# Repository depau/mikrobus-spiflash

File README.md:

# mikroBUS SPI flash module

Sporting 2 removable SPI NOR flash memories, interchangeable. Useful to swap and reprogram the firmware of the GlobalScale MOCHAbin.

The top tiny boards are supposed to be broken off and installed on the pin headers.

The switch allows switching between the two flash memories.

I've ordered the boards but I haven't received/tested them yet.

## License

CERN Open Hardware License, strictly reciprocal.

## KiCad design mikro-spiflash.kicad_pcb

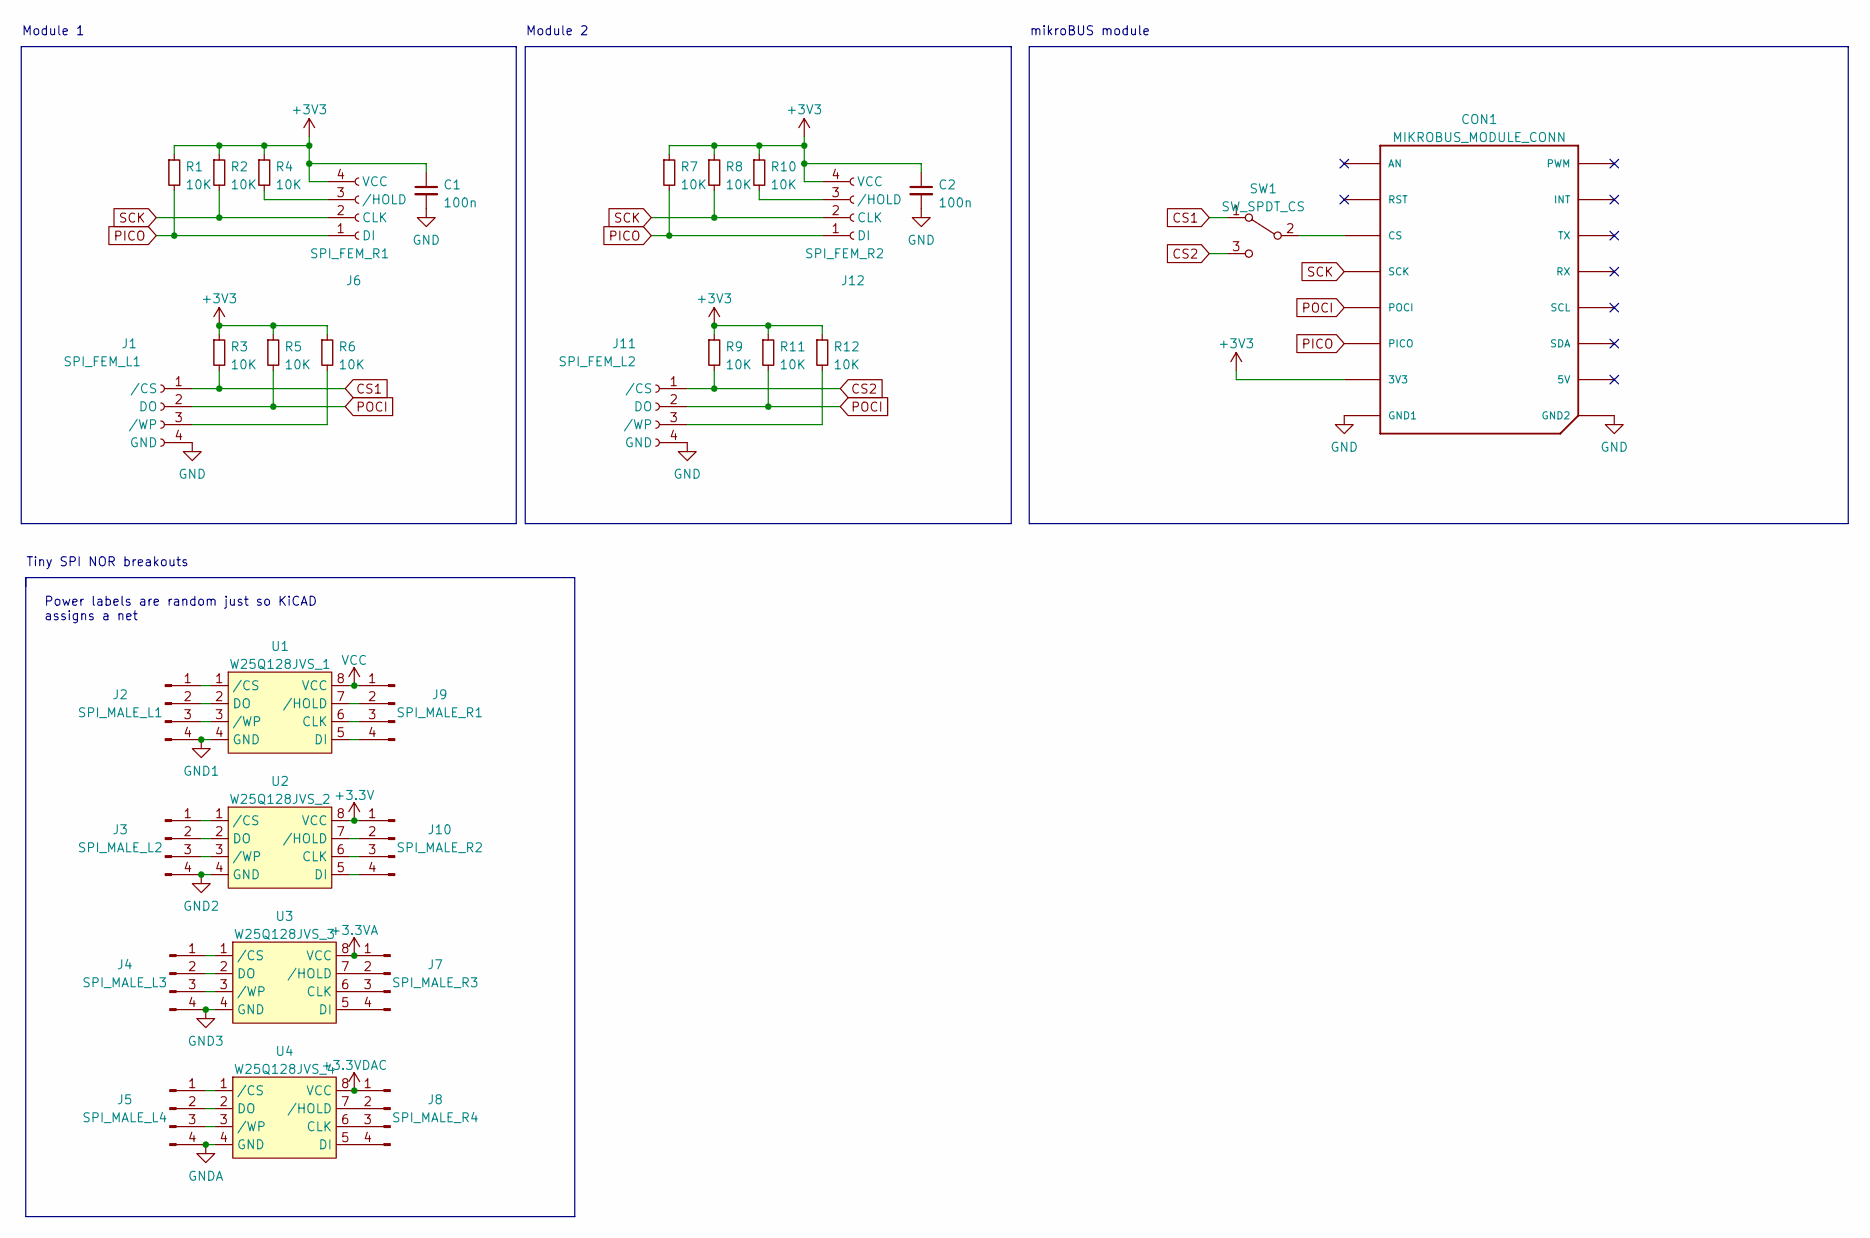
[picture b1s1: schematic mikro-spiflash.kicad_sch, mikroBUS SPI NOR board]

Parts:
C1, C2: 100n; C_0402_1005Metric; JLCPCB BOM 1
CON1: MIKROBUS_MODULE_CONN; JLCPCB BOM 0
J1: SPI_FEM_L1; PinSocket_1x04_P2.54mm_Vertical; JLCPCB BOM 0
J2: SPI_MALE_L1; PinHeader_1x04_P2.54mm_Vertical; JLCPCB BOM 0
J3: SPI_MALE_L2; PinHeader_1x04_P2.54mm_Vertical; JLCPCB BOM 0
J4: SPI_MALE_L3; PinHeader_1x04_P2.54mm_Vertical; JLCPCB BOM 0
J5: SPI_MALE_L4; PinHeader_1x04_P2.54mm_Vertical; JLCPCB BOM 0
J6: SPI_FEM_R1; PinSocket_1x04_P2.54mm_Vertical; JLCPCB BOM 0
J7: SPI_MALE_R3; PinHeader_1x04_P2.54mm_Vertical; JLCPCB BOM 0
J8: SPI_MALE_R4; PinHeader_1x04_P2.54mm_Vertical; JLCPCB BOM 0
J9: SPI_MALE_R1; PinHeader_1x04_P2.54mm_Vertical; JLCPCB BOM 0
J10: SPI_MALE_R2; PinHeader_1x04_P2.54mm_Vertical; JLCPCB BOM 0
J11: SPI_FEM_L2; PinSocket_1x04_P2.54mm_Vertical; JLCPCB BOM 0
J12: SPI_FEM_R2; PinSocket_1x04_P2.54mm_Vertical; JLCPCB BOM 0
R1, R2, R3, R4, R5, R6, R7, R8, R9, R10, R11, R12: 10K; R_0402_1005Metric; JLCPCB BOM 1
SW1: SW_SPDT_CS; SW_MSK12C02-HB; JLCPCB BOM 1
U1: W25Q128JVS_1; SOIC-8_5.23x5.23mm_P1.27mm; JLCPCB BOM 1
U2: W25Q128JVS_2; SOIC-8_5.23x5.23mm_P1.27mm; JLCPCB BOM 1
U3: W25Q128JVS_3; SOIC-8_5.23x5.23mm_P1.27mm; JLCPCB BOM 1
U4: W25Q128JVS_4; SOIC-8_5.23x5.23mm_P1.27mm; JLCPCB BOM 1

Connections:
+3.3V: J10.1, U2.8 (VCC)
+3.3VA: J7.1, U3.8 (VCC)
+3.3VDAC: J8.1, U4.8 (VCC)
+3V3: C1.1, C2.1, CON1.P7 (3V3), J6.4 (VCC), J12.4 (VCC), R1.1, R2.1, R3.1, R4.1, R5.1, R6.1, R7.1, R8.1, R9.1, R10.1, R11.1, R12.1
CS1: J1.1 (/CS), R3.2, SW1.1 (A)
CS2: J11.1 (/CS), R9.2, SW1.3 (C)
GND: C1.2, C2.2, CON1.P8 (GND1), CON1.P9 (GND2), J1.4 (GND), J11.4 (GND)
GND1: J2.4, U1.4 (GND)
GND2: J3.4, U2.4 (GND)
GND3: J4.4, U3.4 (GND)
GNDA: J5.4, U4.4 (GND)
unnamed: CON1.P3 (CS), SW1.2 (B)
unnamed: J1.3 (/WP), R6.2
unnamed: J2.1, U1.1 (/CS)
unnamed: J2.2, U1.2 (DO)
unnamed: J2.3, U1.3 (/WP)
unnamed: J6.3 (/HOLD), R4.2
unnamed: J11.3 (/WP), R12.2
unnamed: J12.3 (/HOLD), R10.2
unnamed: J9.4, U1.5 (DI)
unnamed: J9.3, U1.6 (CLK)
unnamed: J9.2, U1.7 (/HOLD)
unnamed: J3.1, U2.1 (/CS)
unnamed: J3.2, U2.2 (DO)
unnamed: J3.3, U2.3 (/WP)
unnamed: J10.4, U2.5 (DI)
unnamed: J10.3, U2.6 (CLK)
unnamed: J10.2, U2.7 (/HOLD)
unnamed: J4.1, U3.1 (/CS)
unnamed: J4.2, U3.2 (DO)
unnamed: J4.3, U3.3 (/WP)
unnamed: J7.4, U3.5 (DI)
unnamed: J7.3, U3.6 (CLK)
unnamed: J7.2, U3.7 (/HOLD)
unnamed: J5.1, U4.1 (/CS)
unnamed: J5.2, U4.2 (DO)
unnamed: J5.3, U4.3 (/WP)
unnamed: J8.4, U4.5 (DI)
unnamed: J8.3, U4.6 (CLK)
unnamed: J8.2, U4.7 (/HOLD)
PICO: CON1.P6 (PICO), J6.1 (DI), J12.1 (DI), R1.2, R7.2
POCI: CON1.P5 (POCI), J1.2 (DO), J11.2 (DO), R5.2, R11.2
SCK: CON1.P4 (SCK), J6.2 (CLK), J12.2 (CLK), R2.2, R8.2
VCC: J9.1, U1.8 (VCC)

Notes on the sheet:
Power labels are random just so KiCAD assigns a net
Module 2
Tiny SPI NOR breakouts
Module 1
mikroBUS module

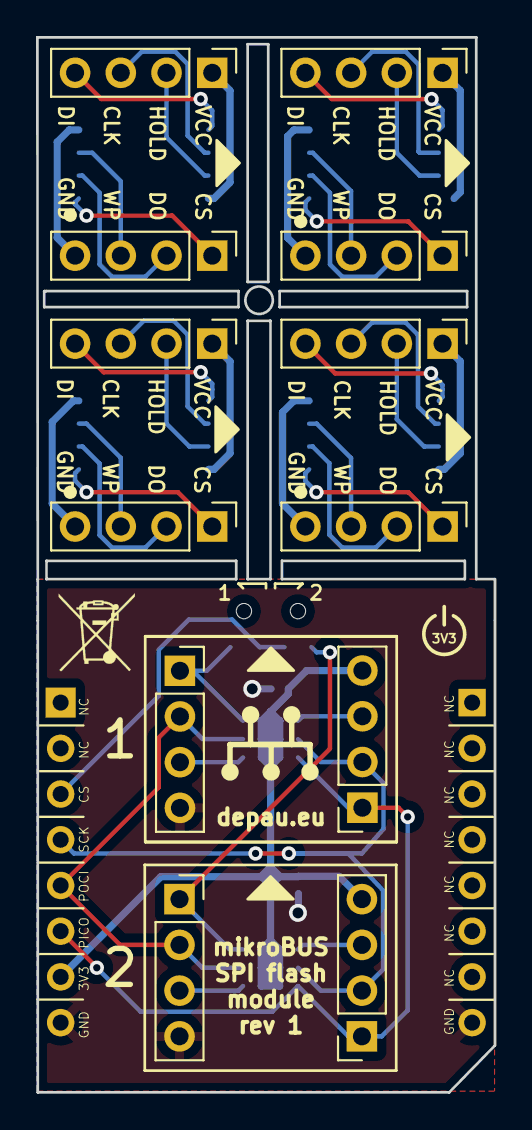
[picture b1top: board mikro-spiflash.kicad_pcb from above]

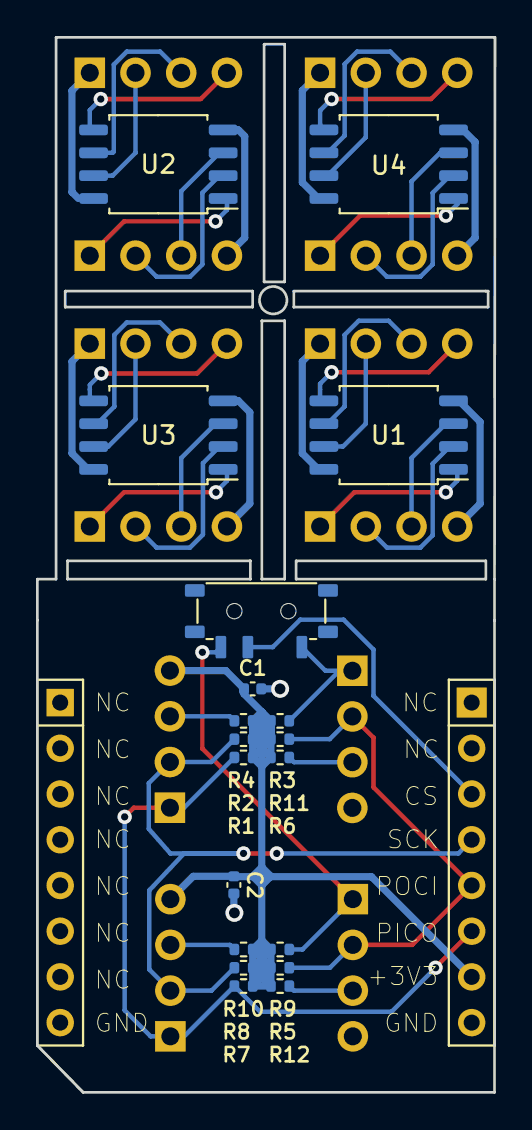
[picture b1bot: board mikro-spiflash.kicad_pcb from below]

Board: 2 copper layers, 25.4 x 58.6 mm, 33 parts (19 on the bottom side), 44 nets.

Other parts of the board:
*: MIKROCLICK_LOGO; MIKROBUS_LOGO

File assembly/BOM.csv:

Comment,Designator,Footprint,LCSC Part #
"100n Unpolarized capacitor, small symbol","C1,C2",C_0402_1005Metric,C1525
"10K Resistor, small symbol","R1,R2,R3,R4,R5,R6,R7,R8,R9,R10,R11,R12",R_0402_1005Metric,C25744
"SW_SPDT_CS Switch, single pole double throw",SW1,SW_MSK12C02-HB,C431541
W25Q128JVS_1 ,U1,SOIC-8_5.23x5.23mm_P1.27mm,C97521
W25Q128JVS_2 ,U2,SOIC-8_5.23x5.23mm_P1.27mm,C97521
W25Q128JVS_3 ,U3,SOIC-8_5.23x5.23mm_P1.27mm,C97521
W25Q128JVS_4 ,U4,SOIC-8_5.23x5.23mm_P1.27mm,C97521
